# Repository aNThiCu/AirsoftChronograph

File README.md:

# Airsoft Chronograph
A chronograph compatible with ESP32 and ESP8266 used for airsoft to get the exit velocity of the bb from the barrel and RPS of the replica(working on the RPS part).

The default ip for accessing the main webpage should be 192.168.5.5.

A pop-up should appear when u connect to the ESP8266 in AP mode , that is the captive portal which will redirect you to the root page, others are /update(OTA Update)
and /webserial(OTA Serial).

Set your BB weight in the .ino file.

Changing BB weight from the captive portal in progress

An assembly guide of the stl files will come.

Will upload updated 3D models for ESP32 compatibility

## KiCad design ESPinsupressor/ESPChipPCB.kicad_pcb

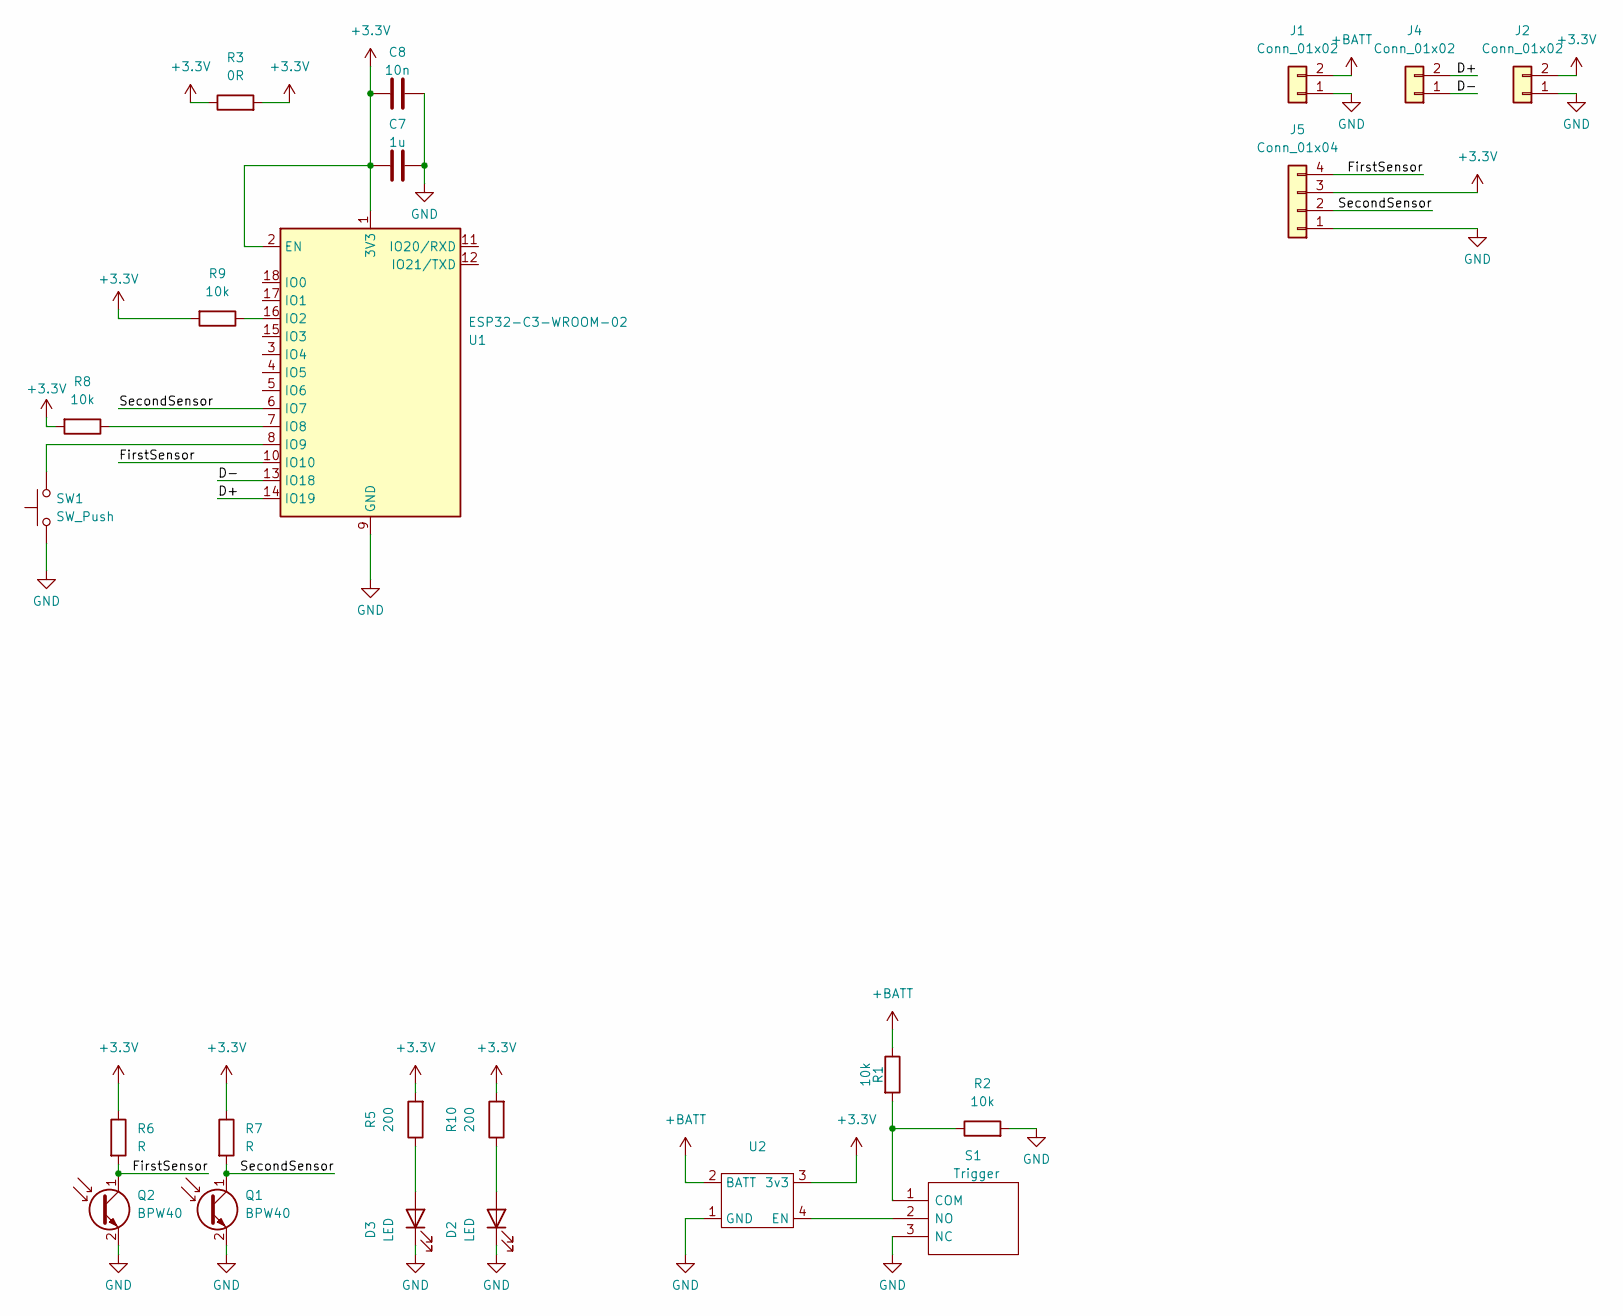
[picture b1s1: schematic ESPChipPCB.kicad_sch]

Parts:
C7: 1u; C_0603_1608Metric
C8: 10n; C_0603_1608Metric
D2, D3: LED; LED_D3.0mm_Clear
J1, J2: Conn_01x02; JST_EH_B2B-EH-A_1x02_P2.50mm_Vertical
J4: Conn_01x02; PinHeader_1x02_P2.54mm_Vertical
J5: Conn_01x04; JST_EH_B4B-EH-A_1x04_P2.50mm_Vertical
Q1, Q2: BPW40; LED_D3.0mm_Clear
R1, R2, R8, R9: 10k; R_0603_1608Metric
R3: 0R; R_1206_3216Metric
R5, R10: 200; R_0603_1608Metric
R6, R7: R; R_0603_1608Metric
S1: Trigger; PinHeader_1x03_P2.54mm_Vertical; Mouser Part Number 710-463092691402
SW1: SW_Push; SolderJumper-2_P1.3mm_Open_RoundedPad1.0x1.5mm
U1: ESP32-C3-WROOM-02
U2: StepDown3v3

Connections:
+3.3V: C7.1, C8.1, J2.2, J5.3, R3.1, R3.2, R5.2, R6.1, R7.1, R8.2, R9.2, R10.2, U1.1 (3V3), U1.2 (EN), U2.3 (3v3)
+BATT: J1.2, R1.1, U2.2 (BATT)
/D+: J4.2, U1.14 (IO19)
/D-: J4.1, U1.13 (IO18)
/FirstSensor: J5.4, Q2.1 (C), R6.2, U1.10 (IO10)
/SecondSensor: J5.2, Q1.1 (C), R7.2, U1.6 (IO7)
GND: C7.2, C8.2, D2.1 (K), D3.1 (K), J1.1, J2.1, J5.1, Q1.2 (E), Q2.2 (E), R2.2, S1.3 (NC), SW1.1, U1.9 (GND), U1.19 (GND), U2.1 (GND)
unnamed: D2.2 (A), R10.1
unnamed: D3.2 (A), R5.1
unnamed: R1.2, R2.1, S1.1 (COM)
unnamed: S1.2 (NO), U2.4 (EN)
unnamed: R9.1, U1.16 (IO2)
unnamed: R8.1, U1.7 (IO8)
unnamed: SW1.2, U1.8 (IO9)

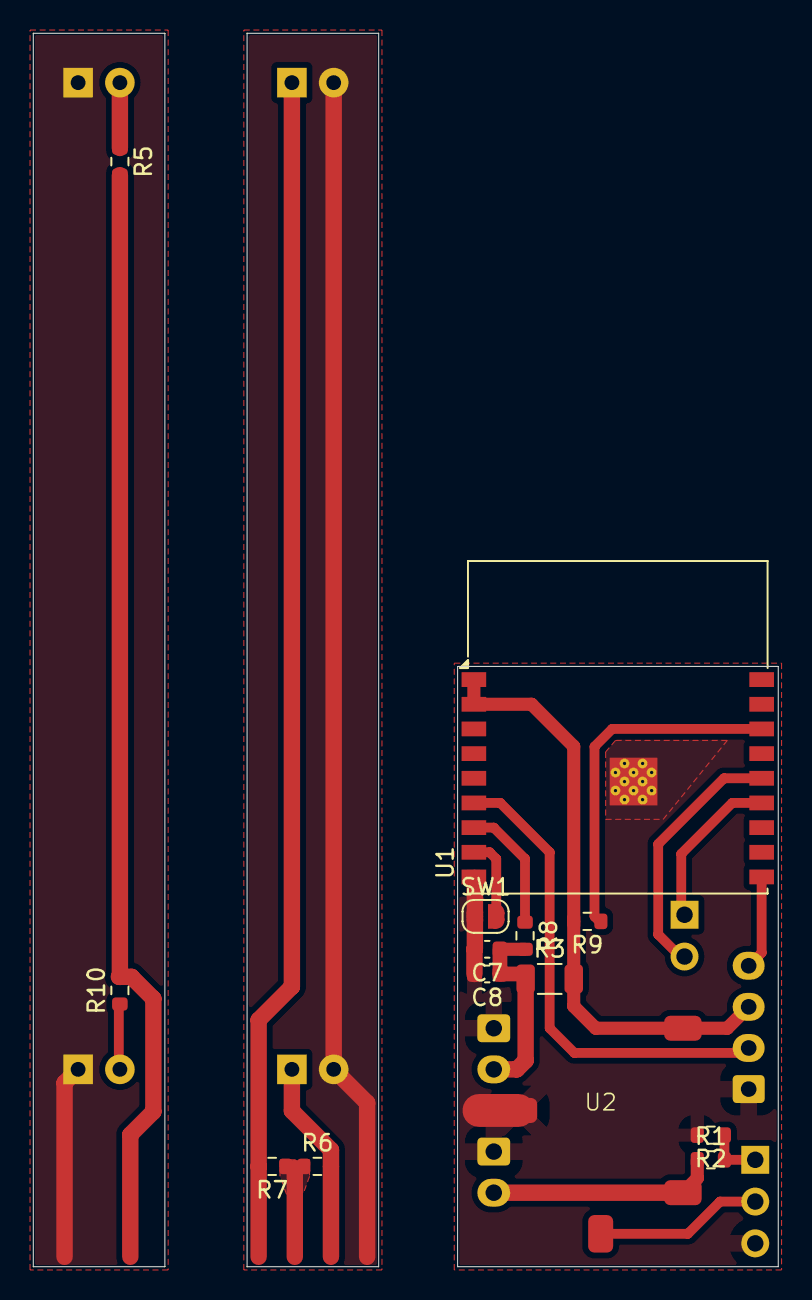
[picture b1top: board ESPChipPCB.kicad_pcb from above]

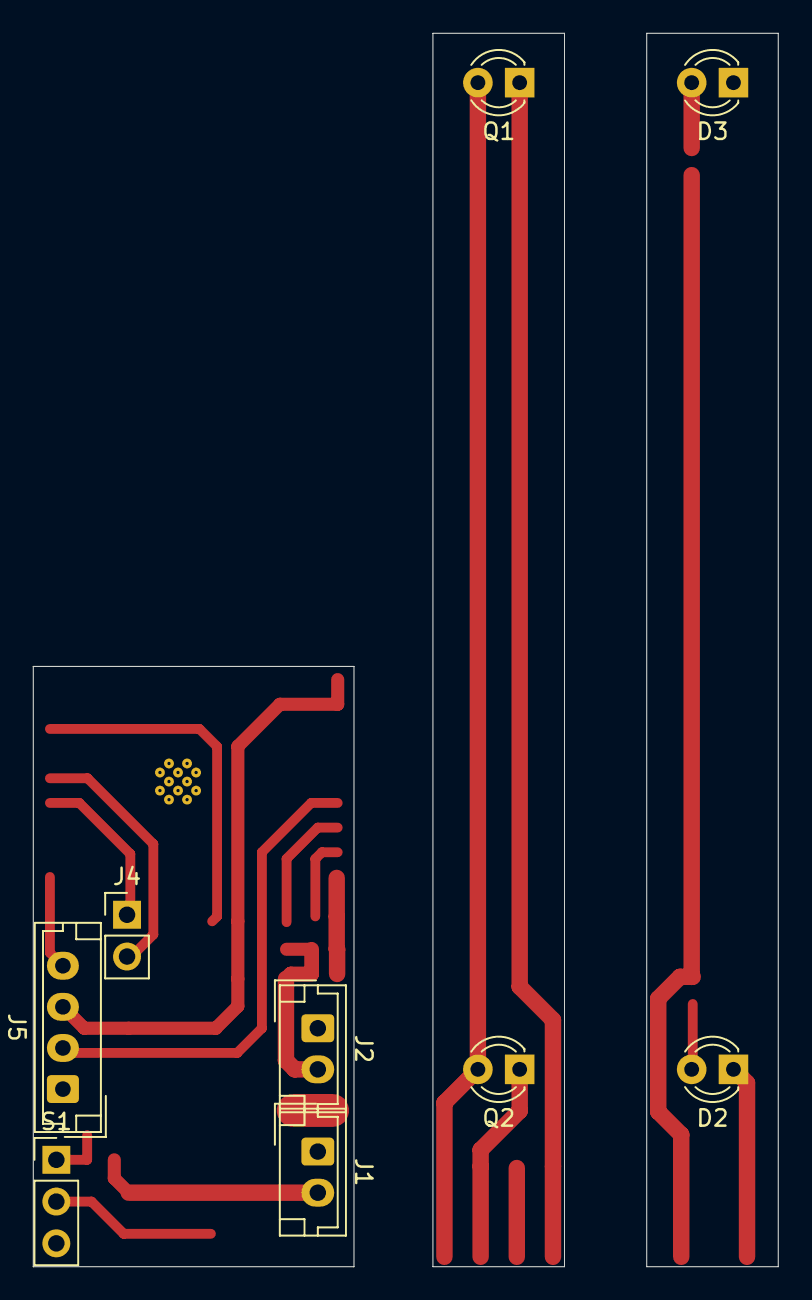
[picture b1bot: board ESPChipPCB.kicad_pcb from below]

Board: 2 copper layers, 45.3 x 75.0 mm, 23 parts (9 on the bottom side), 14 nets.

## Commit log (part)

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2025-03-07 complete rewrite of communication between client and server
2025-03-07 added models for ESP32
2025-03-10 started development on PCB version
2025-07-02 More pcb stuff
2025-07-15 Moved from arduino to platformio , redone some of the code
2025-07-19 Redone logic and calculations
2025-08-05 Added supressor variant
2025-08-19 fixes
2026-04-28 small changes
